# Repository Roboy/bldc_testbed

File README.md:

for dshot use https://github.com/gueei/DShot-Arduino

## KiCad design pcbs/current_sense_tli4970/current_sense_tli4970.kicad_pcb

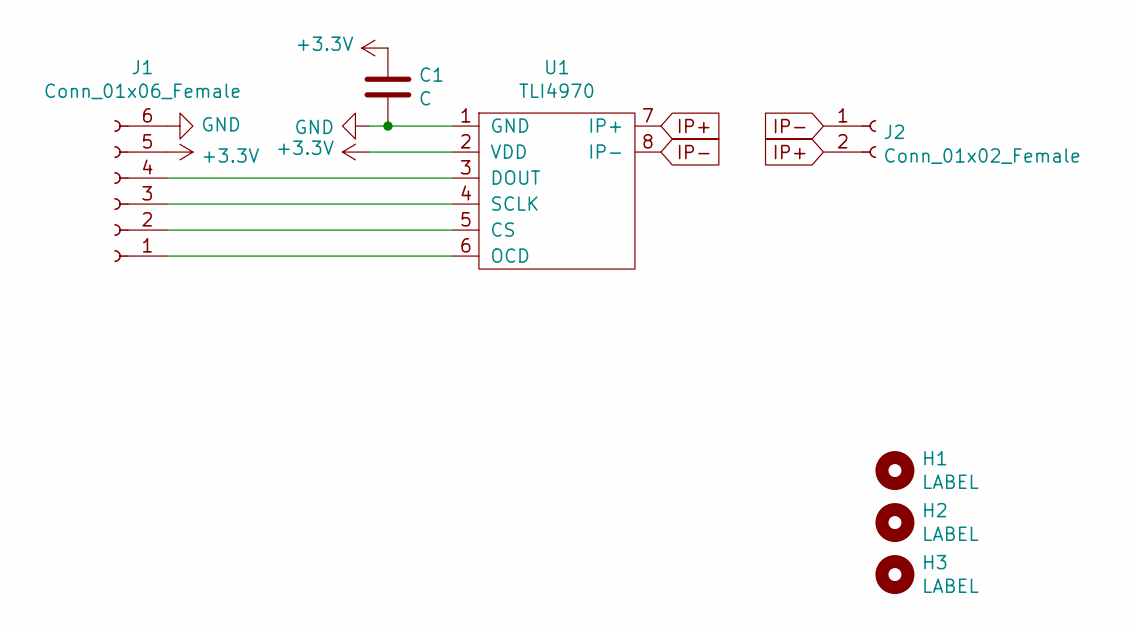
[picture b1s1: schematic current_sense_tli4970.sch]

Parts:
C1: C; C_0402_1005Metric
H1: LABEL; R1_ear_silk_5.5mm
H2: LABEL; R1_eyes_mask_5.5mm
H3: LABEL; R1_face_mask_5.5mm
J1: Conn_01x06_Female; TE-Connectivity_Micro-Match_connector_02x03_Pitch_1.27mm
J2: Conn_01x02_Female; Wago_2060_2_SMD
U1: TLI4970

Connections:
+3V3: C1.1, J1.5, U1.2 (VDD)
GND: C1.2, J1.6, U1.1 (GND)
IP+: J2.2, U1.7 (IP+)
IP-: J2.1, U1.8 (IP-)
unnamed: J1.1, U1.6 (OCD)
unnamed: J1.2, U1.5 (CS)
unnamed: J1.3, U1.4 (SCLK)
unnamed: J1.4, U1.3 (DOUT)

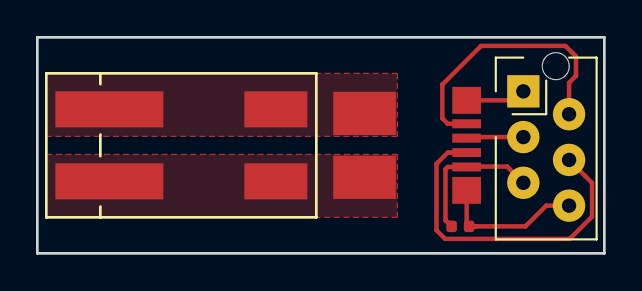
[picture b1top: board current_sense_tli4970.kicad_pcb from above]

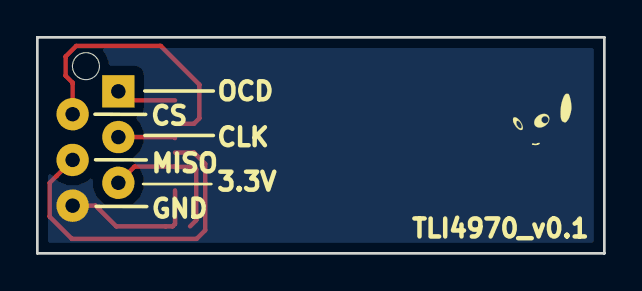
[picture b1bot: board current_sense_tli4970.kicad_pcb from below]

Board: 2 copper layers, 31.5 x 12.0 mm, 7 parts (3 on the bottom side), 8 nets.

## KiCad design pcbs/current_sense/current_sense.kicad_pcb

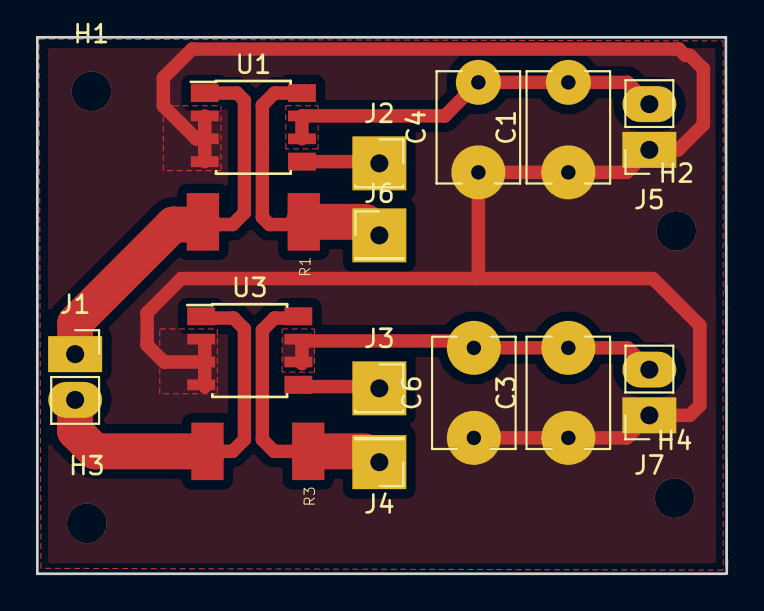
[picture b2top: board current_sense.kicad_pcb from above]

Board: 2 copper layers, 38.3 x 29.8 mm, 19 parts (0 on the bottom side), 7 nets.

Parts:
C1, C3: 1u; C_Disc_D6.0mm_W4.4mm_P5.00mm
C4, C6: 10u; C_Disc_D6.0mm_W4.4mm_P5.00mm
H1, H2, H3, H4: MountingHole; MountingHole_2.2mm_M2
J1, J5, J7: Conn_01x02_Female; PinSocket_1x02_P2.54mm_Vertical
J2, J3: Conn_01x01_Female; PinSocket_1x01_P2.54mm_Vertical
J4, J6: Conn_01x01_Male; PinHeader_1x01_P2.54mm_Vertical
R1, R3: SHUNT; R2512_shunt
U1, U3: AD8207; SOIC-8_3.9x4.9mm_P1.27mm

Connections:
+3V3: C1.2, C3.2, C4.2, C6.2, J5.2, J7.2, U1.6, U1.7, U3.6, U3.7
CURRENT_1: J3.1, U1.5
GND: C1.1, C3.1, C4.1, C6.1, H1.1, H2.1, H3.1, H4.1, J5.1, J7.1, U1.2, U1.3, U1.4, U3.2, U3.3, U3.4
PHASE0_IN: J1.2, R3.2, U3.1
PHASE0_OUT: J4.1, R3.1, U3.8
PHASE1_IN: J1.1, R1.2, U1.1
PHASE1_OUT: J6.1, R1.1, U1.8

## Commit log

2019-11-26 schematics
2019-11-28 added arduino reference for foc https://github.com/askuric/Arduino-FOC
2019-11-28 with angle sensor and commutation
2019-11-29 controlling each phase via serial commands
2019-12-02 first draft auto-phase
2019-12-06 with current sensors
2020-02-23 with esc control using arduino servo library
2020-03-01 dshot example
2020-05-09 with dshot lib
